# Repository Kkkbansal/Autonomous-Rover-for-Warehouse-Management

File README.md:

# Autonomous Rover for Warehouse Rack Inventory Management System

An intelligent autonomous rover designed for **real-time warehouse inventory auditing and management**, developed for **Inter IIT Tech Meet 14.0**.

The system performs **autonomous navigation, vertical rack scanning, QR-code detection, and real-time inventory reporting**, reducing manual audit cycles from **1–2 weeks to just 1 day** with **<1% discrepancy**.

---

## Project Overview

Warehouse inventory auditing is traditionally slow, labor-intensive, and error-prone.

This project introduces an **end-to-end autonomous scanning rover** capable of:

- Autonomous warehouse navigation
- Rack-level vertical scanning
- High-accuracy QR/barcode detection
- Real-time inventory status updates
- Low discrepancy stock verification

---

## Key Performance Targets

| Metric | Target |
|---------|--------|
| Horizontal Position Accuracy | ±10 cm |
| Vertical Position Accuracy | ±2 cm |
| Image Resolution | 1080p |
| QR Detection Reliability | >95% |
| Audit Cycle Time | 1 Day |
| Inventory Discrepancy | <1% |

---

## System Architecture

The rover consists of the following major subsystems:

- **Chassis System**
- **Differential Drive Mechanism**
- **Vertical Scissor Lift**
- **Power Management System**
- **Control System**
- **Path Planning Module**
- **QR Code Scanning Module**
- **Human Machine Interface (HMI)**

---

## Hardware Specifications

### Rover Specifications

- **Dimensions:** 600 × 355 mm
- **Weight:** ~20 kg
- **Rack Coverage:** 5 shelf levels
- **Vision Height Range:** 0.14 m – 1.75 m
- **Drive:** 2-wheel differential drive
- **Support:** Front and rear casters
- **Lift Mechanism:** 4-stage scissor lift
- **Battery:** 18V rechargeable battery
- **Backup Capacity:** 22000 mAh
- **Operational Time:** Up to 4 hours

---

## Sensors & Computing

- **Intel RealSense D455** for depth sensing and navigation
- **1080p Camera** for QR-code scanning
- **Jetson AGX Xavier** for high-level control and processing
- **ESP32** for real-time low-level motor control

---

## Mechanical Design

### Chassis

- Modular T-slot architecture
- High structural rigidity
- Controlled flexibility for uneven floors
- Optimized load distribution

### Drive System

- Differential drive configuration
- Zero-radius turning
- High traction wheel placement
- Robust caster-based stability

### Vertical System

A **4-stage pantograph scissor lift** is used for vertical scanning.

### Why Scissor Lift?

- Fully collapsible
- Compact design
- High vertical precision
- Safe for narrow aisle movement
- Easy field maintenance

---

## Control Architecture

The control system follows a **two-tier hierarchical structure**:

### High-Level Control
- Jetson AGX Xavier
- ROS2 (Cyclone DDS)
- Path planning
- Object detection
- QR scanning
- System supervision

### Low-Level Control
- ESP32
- PID-based motor control
- Encoder feedback processing
- Real-time closed-loop control

---

## Software Stack

- **ROS2**
- **Python**
- **C++**
- **OpenCV**
- **ESP32 Firmware**
- **MATLAB PID tuning**
- **Jetson SDK**

---

## Features

- Autonomous navigation
- Real-time mapping
- QR code scanning
- Inventory mismatch detection
- Rack height scanning
- Live bot telemetry
- Battery diagnostics
- Wi-Fi quality monitoring
- Remote start / pause / restart controls

---

## Human Machine Interface (HMI)

The HMI dashboard provides:

- Bot live status
- Battery health
- Wi-Fi status
- Live camera feed
- Sensor telemetry
- Start / stop scan controls
- Inventory alerts
- Success / caution notifications

---

## Future Improvements

### 1. Multi-Robot Swarm Coordination
Enable multiple autonomous rovers with centralized planning and distributed execution.

### 2. Enhanced Sensor Suite
Integrate:
- LiDAR
- Ultrasonic sensors
- Radar
- Thermal imaging

### 3. Robotic Arm Integration
Add manipulation capabilities for:
- pick and place
- object repositioning
- multi-angle scanning

---

## Applications

- Smart warehouses
- Inventory automation
- Industrial logistics
- E-commerce fulfillment centers
- Manufacturing storage systems

---

## Team

**Inter IIT Tech Meet 14.0**

Project: *Autonomous Rover for Warehouse Rack Inventory Management System*

---

## Acknowledgments

Special thanks to the Inter IIT Tech Meet organizers, mentors, and team members for their support in the development of this project.

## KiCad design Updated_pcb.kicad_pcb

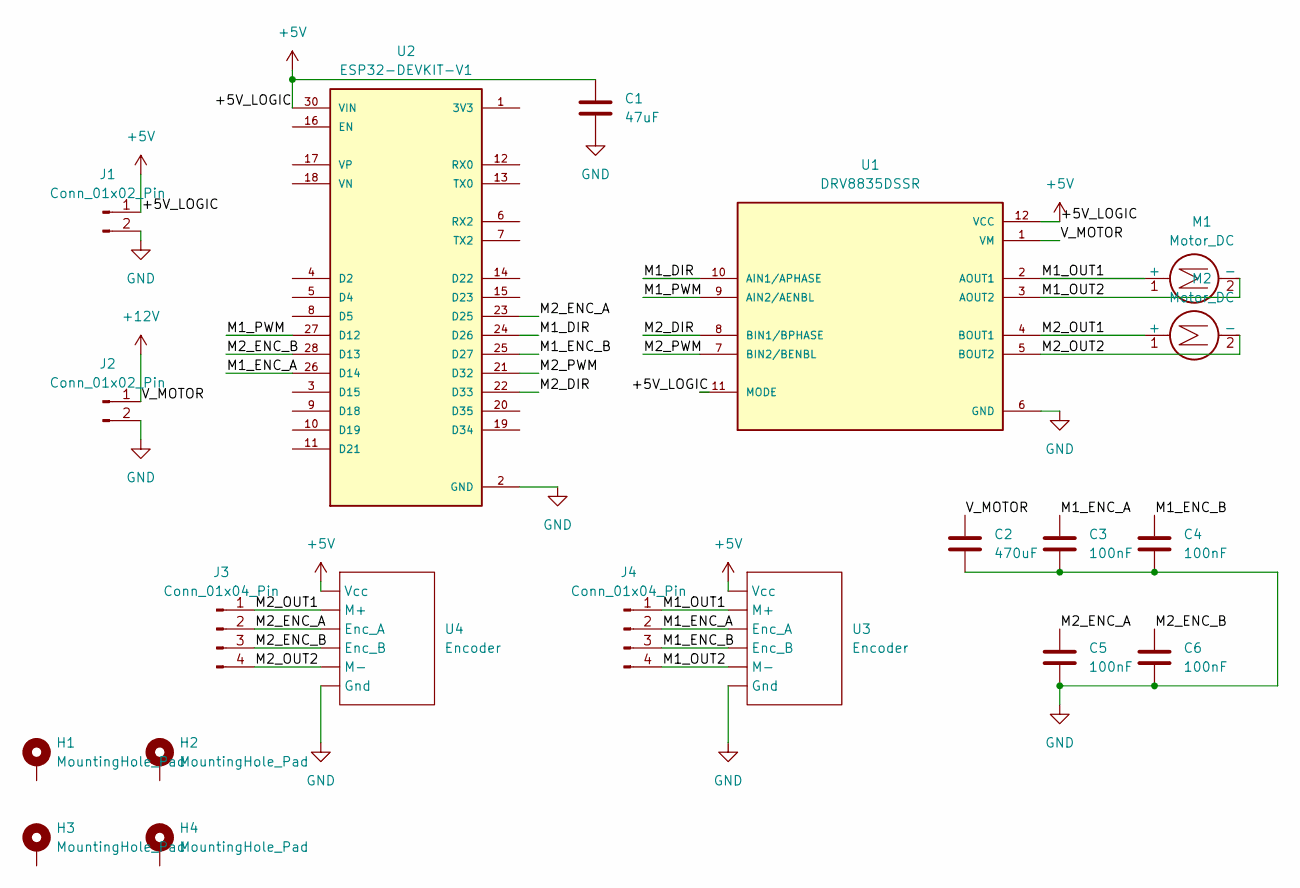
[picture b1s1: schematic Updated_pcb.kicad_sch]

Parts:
C1: 47uF; C_Radial_D5.0mm_H7.0mm_P2.00mm
C2: 470uF; C_Radial_D5.0mm_H7.0mm_P2.00mm
C3, C4, C5, C6: 100nF; C_Radial_D5.0mm_H7.0mm_P2.00mm
H1, H2, H3, H4: MountingHole_Pad; MountingHole_2.2mm_M2_ISO7380_Pad_TopBottom
J1, J2: Conn_01x02_Pin; PinHeader_1x02_P1.00mm_Vertical_SMD_Pin1Left
J3, J4: Conn_01x04_Pin; PinHeader_1x04_P1.00mm_Vertical_SMD_Pin1Left
M1, M2: Motor_DC; PinHeader_2x01_P2.54mm_Vertical_SMD
U1: DRV8835DSSR; SON50P300X200X80-13N; PARTREV H
U2: ESP32-DEVKIT-V1; MODULE_ESP32_DEVKIT_V1; PARTREV N/A
U3, U4: Encoder

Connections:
+5V: C1.2, J1.1, U1.11 (MODE), U1.12 (VCC), U2.30 (VIN), U3., U4.
+12V: C2.1, J2.1, U1.1 (VM)
/M1_DIR: U1.10 (AIN1/APHASE), U2.24 (D26)
/M1_ENC_A: C3.1, J4.2, U2.26 (D14), U3.
/M1_ENC_B: C4.1, J4.3, U2.25 (D27), U3.
/M1_OUT1: J4.1, M1.1 (+), U1.2 (AOUT1), U3.
/M1_OUT2: J4.4, M1.2 (-), U1.3 (AOUT2), U3.
/M1_PWM: U1.9 (AIN2/AENBL), U2.27 (D12)
/M2_DIR: U1.8 (BIN1/BPHASE), U2.22 (D33)
/M2_ENC_A: C5.1, J3.2, U2.23 (D25), U4.
/M2_ENC_B: C6.1, J3.3, U2.28 (D13), U4.
/M2_OUT1: J3.1, M2.1 (+), U1.4 (BOUT1), U4.
/M2_OUT2: J3.4, M2.2 (-), U1.5 (BOUT2), U4.
/M2_PWM: U1.7 (BIN2/BENBL), U2.21 (D32)
GND: C1.1, C2.2, C3.2, C4.2, C5.2, C6.2, J1.2, J2.2, U1.6 (GND), U1.13 (GND), U2.2 (GND), U2.29 (GND), U3., U4.

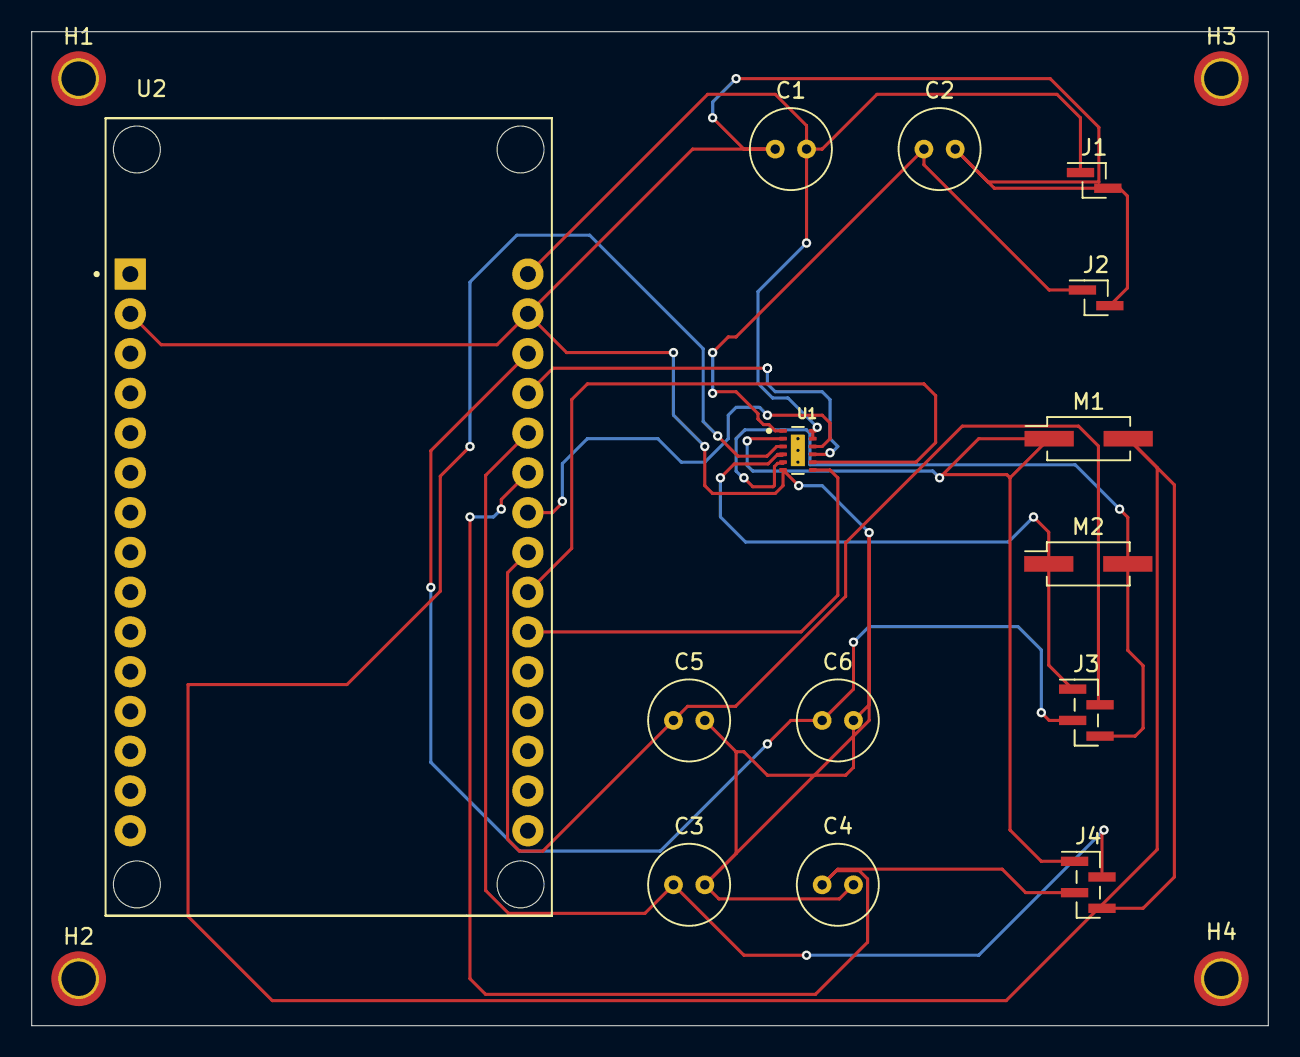
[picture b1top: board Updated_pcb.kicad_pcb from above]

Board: 2 copper layers, 79.0 x 63.5 mm, 18 parts (0 on the bottom side), 15 nets.

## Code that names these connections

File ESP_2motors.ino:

#include <Arduino.h>

// ===================== PIN DEFINITIONS =====================

// -------- Motor 1 pins --------
#define M1_PWM   25        // PWM pin
#define M1_DIR   26        // DIR pin
#define M1_ENC_A 35        // Encoder A
#define M1_ENC_B 13        // Encoder B

// -------- Motor 2 pins --------
#define M2_PWM   33       // PWM pin
#define M2_DIR   32        // DIR pin
#define M2_ENC_A 27        // Encoder A
#define M2_ENC_B 14        // Encoder B

// ==================== ENCODER VARIABLES ====================

volatile long enc1Count = 0;
volatile uint8_t prev1State = 0;

volatile long enc2Count = 0;
volatile uint8_t prev2State = 0;

// =================== MOTOR / PID PARAMETERS =================

const int ppr_mech = 325;
const int ppr_4x   = ppr_mech * 4;

// PID values
float Kp = 2.35f;
float Ki = 3.875f;
float Kd = 0.415f;

float integMin = -50.0f;
float integMax =  50.0f;

// PID states M1
float err1=0, prevErr1=0, integ1=0, dFiltered1=0;
float rpmFiltered1 = 0;

// PID states M2
float err2=0, prevErr2=0, integ2=0, dFiltered2=0;
float rpmFiltered2 = 0;

// Filters
const float rpmAlpha = 0.3f;
const float dAlpha   = 0.15f;

// Setpoints
float setRpm1 = 50.0f;
float setRpm2 = 50.0f;

// Timing
unsigned long lastTs = 0;
const unsigned long Ts_ms = 10;


// ====================== QUADRATURE ISR M1 =====================
void IRAM_ATTR enc1ISR() {
  uint8_t state = (digitalRead(M1_ENC_A) << 1) | digitalRead(M1_ENC_B);

  if ((prev1State == 0b00 && state == 0b01) ||
      (prev1State == 0b01 && state == 0b11) ||
      (prev1State == 0b11 && state == 0b10) ||
      (prev1State == 0b10 && state == 0b00))
    enc1Count++;
  else if ((prev1State == 0b00 && state == 0b10) ||
           (prev1State == 0b10 && state == 0b11) ||
           (prev1State == 0b11 && state == 0b01) ||
           (prev1State == 0b01 && state == 0b00))
    enc1Count--;

  prev1State = state;
}

// ====================== QUADRATURE ISR M2 =====================
void IRAM_ATTR enc2ISR() {
  uint8_t state = (digitalRead(M2_ENC_A) << 1) | digitalRead(M2_ENC_B);

  if ((prev2State == 0b00 && state == 0b01) ||
      (prev2State == 0b01 && state == 0b11) ||
      (prev2State == 0b11 && state == 0b10) ||
      (prev2State == 0b10 && state == 0b00))
    enc2Count++;
  else if ((prev2State == 0b00 && state == 0b10) ||
           (prev2State == 0b10 && state == 0b11) ||
           (prev2State == 0b11 && state == 0b01) ||
           (prev2State == 0b01 && state == 0b00))
    enc2Count--;

  prev2State = state;
}

// ====================== MOTOR HELPER =========================
void setMotor(int pwmPin, int dirPin, int val) {
  val = constrain(val, -255, 255);

  if (val >= 0) {
    digitalWrite(dirPin, LOW);
    analogWrite(pwmPin, val);
  } else {
    digitalWrite(dirPin, HIGH);
    analogWrite(pwmPin, -val);
  }
}

float pulsesToRpm(long pulses, int ppr4x, unsigned long dt_ms) {
  float dt = dt_ms / 1000.0f;
  return (pulses / (float)ppr4x) * (60.0f / dt);
}

// ============================= SETUP =========================
void setup() {
  Serial.begin(115200);

  pinMode(M1_PWM, OUTPUT);
  pinMode(M1_DIR, OUTPUT);
  pinMode(M2_PWM, OUTPUT);
  pinMode(M2_DIR, OUTPUT);

  pinMode(M1_ENC_A, INPUT);
  pinMode(M1_ENC_B, INPUT_PULLUP);

  pinMode(M2_ENC_A, INPUT);
  pinMode(M2_ENC_B, INPUT_PULLUP);

  prev1State = (digitalRead(M1_ENC_A) << 1) | digitalRead(M1_ENC_B);
  prev2State = (digitalRead(M2_ENC_A) << 1) | digitalRead(M2_ENC_B);

  attachInterrupt(M1_ENC_A, enc1ISR, CHANGE);
  attachInterrupt(M1_ENC_B, enc1ISR, CHANGE);
  attachInterrupt(M2_ENC_A, enc2ISR, CHANGE);
  attachInterrupt(M2_ENC_B, enc2ISR, CHANGE);

  lastTs = millis();
}

// ============================== LOOP ==========================
void loop() {

  unsigned long now = millis();
  if (now - lastTs >= Ts_ms) {

    unsigned long dt = now - lastTs;
    lastTs = now;

    long p1 = enc1Count; enc1Count = 0;
    long p2 = enc2Count; enc2Count = 0;

    float rpm1 = pulsesToRpm(p1, ppr_4x, dt);
    float rpm2 = pulsesToRpm(p2, ppr_4x, dt);

    rpmFiltered1 = rpmAlpha * rpm1 + (1 - rpmAlpha) * rpmFiltered1;
    rpmFiltered2 = rpmAlpha * rpm2 + (1 - rpmAlpha) * rpmFiltered2;

    float dt_s = dt / 1000.0f;

    // ===== Motor 1 PID =====
    err1 = setRpm1 - rpmFiltered1;
    integ1 += err1 * dt_s;
    integ1 = constrain(integ1, integMin, integMax);
    float dRaw1 = (err1 - prevErr1) / dt_s;
    dFiltered1 = dAlpha * dRaw1 + (1 - dAlpha) * dFiltered1;
    int out1 = (int)(Kp*err1 + Ki*integ1 + Kd*dFiltered1);
    prevErr1 = err1;

    // ===== Motor 2 PID =====
    err2 = setRpm2 - rpmFiltered2;
    integ2 += err2 * dt_s;
    integ2 = constrain(integ2, integMin, integMax);
    float dRaw2 = (err2 - prevErr2) / dt_s;
    dFiltered2 = dAlpha * dRaw2 + (1 - dAlpha) * dFiltered2;
    int out2 = (int)(Kp*err2 + Ki*integ2 + Kd*dFiltered2);
    prevErr2 = err2;

    // Apply outputs
    setMotor(M1_PWM, M1_DIR, out1);
    setMotor(M2_PWM, M2_DIR, out2);

    // Plotter-friendly output
    Serial.print("M1_set:"); Serial.print(setRpm1);
    Serial.print("\tM1_RPM:"); Serial.print(rpmFiltered1);
    Serial.print("\tM1_out:"); Serial.print(out1);

    Serial.print("\tM2_set:"); Serial.print(setRpm2);
    Serial.print("\tM2_RPM:"); Serial.print(rpmFiltered2);
    Serial.print("\tM2_out:"); Serial.println(out2);
  }
}

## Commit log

2026-04-01 Create Ros_arduino bridge
